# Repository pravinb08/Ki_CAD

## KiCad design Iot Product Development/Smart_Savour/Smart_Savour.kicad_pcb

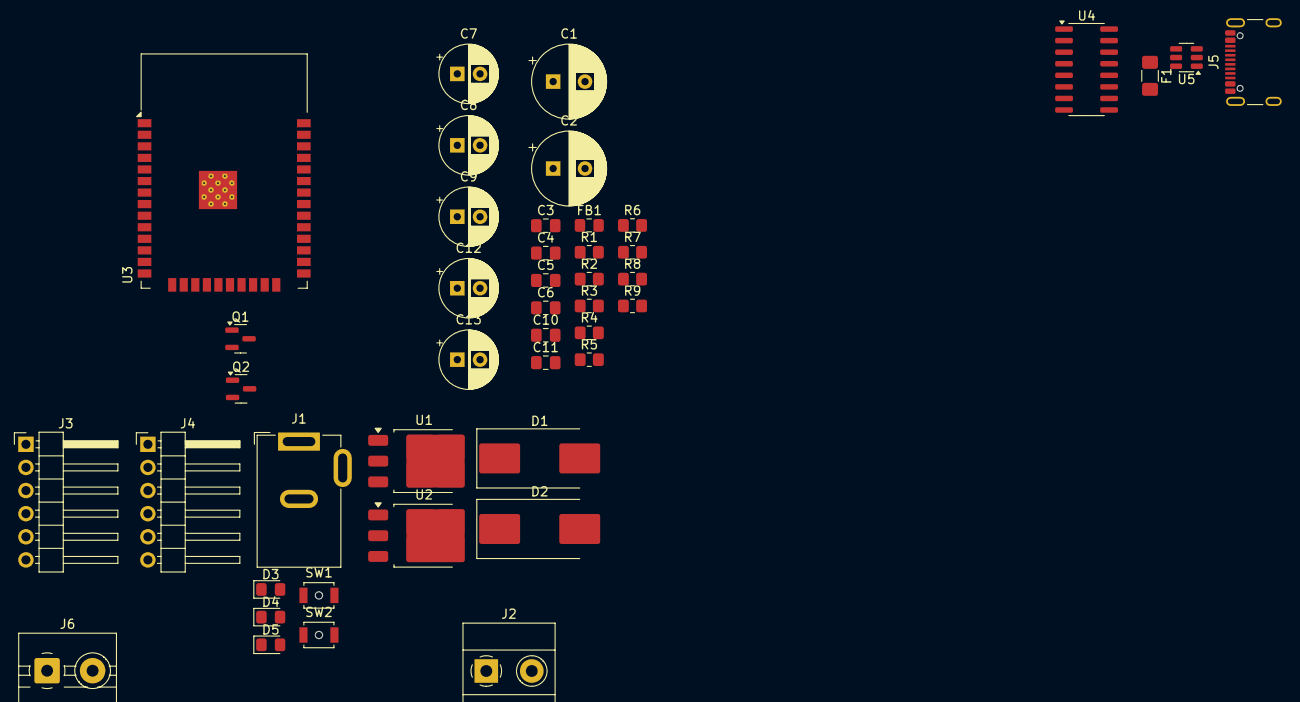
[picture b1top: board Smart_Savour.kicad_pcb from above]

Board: 2 copper layers, 44 parts (0 on the bottom side), 29 nets, no tracks yet.

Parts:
C1: 100uF/63V_THT; CP_Radial_D8.0mm_P3.50mm
C2: 100uF/25V_THT; CP_Radial_D8.0mm_P3.50mm
C3, C4, C5, C6, C10, C11: 0.1uF_0805; C_0805_2012Metric_Pad1.18x1.45mm_HandSolder
C7, C8: 10uF/25V_THT; CP_Radial_D6.3mm_P2.50mm
C9, C12, C13: 10uF; CP_Radial_D6.3mm_P2.50mm
D1, D2: SS54; D_SMC_Handsoldering
D3, D4, D5: Red_0805; LED_0805_2012Metric_Pad1.15x1.40mm_HandSolder
F1: Polyfuse; Fuse_1206_3216Metric_Pad1.42x1.75mm_HandSolder
FB1: FerriteBead; L_0805_2012Metric_Pad1.15x1.40mm_HandSolder
J1: 12V DC; BarrelJack_GCT_DCJ200-10-A_Horizontal
J2: 5V DC; TerminalBlock_Phoenix_MKDS-1,5-2_1x02_P5.00mm_Horizontal
J3: DWIN interface; PinHeader_1x06_P2.54mm_Horizontal
J4: Programming Interface; PinHeader_1x06_P2.54mm_Horizontal
J5: USB_C_Receptacle_USB2.0_16P; USB_C_Receptacle_GCT_USB4105-xx-A_16P_TopMnt_Horizontal
J6: TerminalBlock_MaiXu_MX126-5.0-02P_1x02_P5.00mm
Q1, Q2: BC817; SOT-23
R1, R2, R5: 470_0805; R_0805_2012Metric_Pad1.20x1.40mm_HandSolder
R3, R4: 10K_0805; R_0805_2012Metric_Pad1.20x1.40mm_HandSolder
R6, R7, R8, R9: 10k_0805; R_0805_2012Metric_Pad1.20x1.40mm_HandSolder
SW1, SW2: SW_Push; SW_SPST_B3U-1000P-B
U1: LM1117MP-5; TO-252-3_TabPin2
U2: LM1117MP-3.3; TO-252-3_TabPin2
U3: ESP32-WROOM-32
U4: CH340C; SOIC-16_3.9x9.9mm_P1.27mm
U5: WE-TVS-82400102; SOT-23-6

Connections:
+3.3V: C6.1, C8.1, C11.1, C12.1, FB1.1, J4.5 (3.3), R2.1, U2.2 (VO), U4.4 (V3), U4.16 (VCC)
+5V: C2.1, C4.1, C5.1, C7.1, D2.1 (K), J3.1 (+5v), J6.1, R1.1, U1.2 (VO), U2.3 (VI)
+12V: C1.1, C3.1, D1.1 (K), U1.3 (VI)
/+5v Bus: C13.1, F1.1, J5.A4 (VBUS), J5.A9 (VBUS), J5.B4 (VBUS), J5.B9 (VBUS), U5.5
/Boot: J4.1 (Boot), Q2.2 (E), R4.2, SW2.1, U3.25 (IO0)
/DTR: Q2.3 (C), R6.2, U4.13 (~DTR)
/D_N: U4.6 (UD-), U5.6
/D_P: U4.5 (UD+), U5.4
/En: J4.4 (EN), Q1.3 (C), R3.2, SW1.2, U3.3 (EN)
/RTS: Q1.2 (E), R7.2, U4.14 (~RTS)
/RXD2: J3.4 (TX2), U3.27 (IO16)
/Rx: J4.2 (Rx), U3.34 (RXD0/IO3), U4.2 (TXD)
/TXD2: J3.3 (RX2), U3.28 (IO17)
/Tx: J4.3 (Tx), U3.35 (TXD0/IO1), U4.3 (RXD)
GNDREF: C1.2, C2.2, C3.2, C4.2, C5.2, C6.2, C7.2, C8.2, C9.2, C10.2, C11.2, C12.2, C13.2, D3.1 (K), D4.1 (K), D5.1 (K), J1.2, J2.2, J3.6 (GND), J4.6 (GND), J5.A1 (GND), J5.A12 (GND), J5.B1 (GND), J5.B12 (GND), J5.S1 (SHIELD), R8.1, R9.1, SW1.1, SW2.2, U1.1 (GND), U2.1 (GND), U3.1 (GND), U3.15 (GND), U3.38 (GND), U3.39 (GND), U4.1 (GND), U5.2
unnamed: D1.2 (A), J1.1
unnamed: D2.2 (A), J2.1
unnamed: D3.2 (A), R1.2
unnamed: D4.2 (A), R2.2
unnamed: D5.2 (A), R5.1
unnamed: J5.A5 (CC1), R8.2
unnamed: J5.B5 (CC2), R9.2
unnamed: J5.A6 (D+), J5.B6 (D+), U5.3
unnamed: J5.A7 (D-), J5.B7 (D-), U5.1
unnamed: F1.2, J6.2
unnamed: Q1.1 (B), R6.1
unnamed: Q2.1 (B), R7.1
unnamed: R5.2, U3.24 (IO2)
unnamed: C9.1, C10.1, FB1.2, R3.1, R4.1, U3.2 (VDD)

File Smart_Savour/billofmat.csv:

Reference,Value,Datasheet,Footprint,Qty,DNP
C1,100uF/63V_THT,~,Capacitor_THT:CP_Radial_D8.0mm_P3.50mm,1,
C2,100uF/25V_THT,~,Capacitor_THT:CP_Radial_D8.0mm_P3.50mm,1,
"C3,C4,C5,C6,C10,C11",0.1uF_0805,~,Capacitor_SMD:C_0805_2012Metric_Pad1.18x1.45mm_HandSolder,6,
"C7,C8",10uF/25V_THT,~,Capacitor_THT:CP_Radial_D6.3mm_P2.50mm,2,
"C9,C12,C13",10uF,~,Capacitor_THT:CP_Radial_D6.3mm_P2.50mm,3,
"D1,D2",SS54,~,Diode_SMD:D_SMC_Handsoldering,2,
"D3,D4,D5",Red_0805,~,LED_SMD:LED_0805_2012Metric_Pad1.15x1.40mm_HandSolder,3,
F1,Polyfuse,~,Fuse:Fuse_1206_3216Metric_Pad1.42x1.75mm_HandSolder,1,
FB1,FerriteBead,~,Inductor_SMD:L_0805_2012Metric_Pad1.15x1.40mm_HandSolder,1,
J1,12V DC,~,Connector_BarrelJack:BarrelJack_GCT_DCJ200-10-A_Horizontal,1,
J2,5V DC,~,"TerminalBlock_Phoenix:TerminalBlock_Phoenix_MKDS-1,5-2_1x02_P5.00mm_Horizontal",1,
J3,DWIN interface,~,Connector_PinHeader_2.54mm:PinHeader_1x06_P2.54mm_Horizontal,1,
J4,Programming Interface,,Connector_PinHeader_2.54mm:PinHeader_1x06_P2.54mm_Horizontal,1,
J5,USB_C_Receptacle_USB2.0_16P,https://www.usb.org/sites/default/files/documents/usb_type-c.zip,Connector_USB:USB_C_Receptacle_GCT_USB4105-xx-A_16P_TopMnt_Horizontal,1,
J6,~,~,TerminalBlock:TerminalBlock_MaiXu_MX126-5.0-02P_1x02_P5.00mm,1,
"Q1,Q2",BC817,https://www.onsemi.com/pub/Collateral/BC818-D.pdf,Package_TO_SOT_SMD:SOT-23,2,
"R1,R2,R5",470_0805,~,Resistor_SMD:R_0805_2012Metric_Pad1.20x1.40mm_HandSolder,3,
"R3,R4",10K_0805,~,Resistor_SMD:R_0805_2012Metric_Pad1.20x1.40mm_HandSolder,2,
"R6,R7,R8,R9",10k_0805,~,Resistor_SMD:R_0805_2012Metric_Pad1.20x1.40mm_HandSolder,4,
"SW1,SW2",SW_Push,~,Button_Switch_SMD:SW_SPST_B3U-1000P-B,2,
U1,LM1117MP-5,http://www.ti.com/lit/ds/symlink/lm1117.pdf,Package_TO_SOT_SMD:TO-252-3_TabPin2,1,
U2,LM1117MP-3.3,http://www.ti.com/lit/ds/symlink/lm1117.pdf,Package_TO_SOT_SMD:TO-252-3_TabPin2,1,
U3,ESP32-WROOM-32,https://www.espressif.com/sites/default/files/documentation/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,RF_Module:ESP32-WROOM-32,1,
U4,CH340C,https://datasheet.lcsc.com/szlcsc/Jiangsu-Qin-Heng-CH340C_C8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,Package_SO:SOIC-16_3.9x9.9mm_P1.27mm,1,
U5,WE-TVS-82400102,https://www.we-online.com/components/products/datasheet/8240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,Package_TO_SOT_SMD:SOT-23-6,1,

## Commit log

2025-02-16 Updated Schematic
2025-02-16 Updated Schematic PDF file
2025-02-24 Updated Schematic Version 2
2025-03-23 Updated_Version_2
2025-03-23 Folder updated
2025-03-24 Pcb Layout Updated
2025-04-12 updated board
